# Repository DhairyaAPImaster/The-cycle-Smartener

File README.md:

# The Cycle Smartener
**(Makes the cycle kindda smart)**
### By Dhairya

## About "The Cycle Smartener"

So the Cycle smartener or TCS for short is basically this device that i designed that can be fitted on top of (almost) any modern cycle. Btw i made this cause i absolutelly love cycling and yeah having such a device would make the whole ride way more fun and interesting.

I plan on integrating TinyML (later) to also integrate AI into it so that it can do stuff like change the song or answer questions from voice commands. Alsoin next versions i plan on adding bluetooth so that one can connect their device - smart phone or something to it. and an sd card slot for one to put a micro sd in it to add music.

Btw it also has a 2.4inch LCD Display  (to displays whatever needs to be displayed).

## Folder Structure

`firmware/` - ESP32 firmware source code (C++)

`src/` - source files for PCB and CAD

`src/FreeCAD/` - mechanical CAD sources (open the .FCStd in FreeCAD)

`src/KiCAD/` - KiCad project files for the PCB

`Production/` - exports and fab outputs (gerbers, BOM, STLs)

`Production/PCB/` - gerbers, BOM, CPL files

`Production/CAD/` - exported STLs for the case

`images/` - screenshots and photos used in this README

## BOM with non PCB parts as well as PCB parts (with links)

Here's the parts list i kept while designing - both PCB parts and non-PCB components. i used the file `Production/BOM with non PCB parts too.csv` as the source.

| Item | Purpose | Qty | Unit Price (USD) | Total (USD) | Link |
| --- | --- | ---: | ---: | ---: | --- |
| Micro SD 16GB | For storage | 1 | $13.07 | $13.07 | [link](https://robu.in/product/sandisk-ultra-micro-sd-16gb-uhs-i-98mbs-r-class-10-memory-card/) |
| 40 Pin 2.54mm Male and Female Pin Headers | For connecting modules | 1 | $1.25 | $1.25 | [link](https://www.amazon.in/Super-Debug-Headers-Arduino-Prototype/dp/B09MZD3RBF) |
| Micro SD Card Reader Module | For storage/songs | 1 | $0.35 | $0.35 | [link](https://robu.in/product/micro-sd-card-module/) |
| 3mm Red LED | Status/Error Indicator | 11 | $0.01 | $0.10 | [link](https://robu.in/product/3mm-red-dip-led-pack-of-50/) |
| 3mm Green LED | Status/OK Indicator | 7 | $0.02 | $0.11 | [link](https://robu.in/product/5mm-green-surface-mount-led-pack-of-50/) |
| Tactile Push Button Switch 6x6 | Buttons | 1 Pack | $0.16 | $0.16 | [link](https://robu.in/product/6x6x5-tactile-push-button-switch/) |
| 10uF 25V Electrolytic Capacitor (Pack of 12) | Decoupling | 1 Pack | $0.83 | $0.83 | [link](https://www.amazon.in/10uF-25V-Electrolytic-Capacitor-Pack/dp/B08X2NSPZN) |
| 0.1µF Ceramic Capacitor (100nF) | Decoupling | 10 | $0.01 | $0.13 | [link](https://robu.in/product/100nf-50v-disc-capacitor/) |
| 150Ω Through-Hole Resistor | LED Current Limiting | 5 | $0.04 | $0.19 | [link](https://robu.in/product/mf25-150r-multicomp-pro-through-hole-resistor-150-ohm-mf25-series-250-mw-%C2%B1-1-axial-leaded-250-v/) |
| 10kΩ Through-Hole Resistor | Pull-up/Pull-down | 5 | $0.03 | $0.13 | [link](https://robu.in/product/mfr-25frf52-10k-yageo-metal-film-resistors-10k%CF%89-250mw-%C2%B1100ppm-%E2%84%83-%C2%B11-plugind2-4xl6-3mm-through-hole-resistors-rohs/) |
| 18650 Single Cell Holder | Battery Holder | 1 | $0.29 | $0.29 | [link](https://robu.in/product/1-x-18650-cell-box/) |
| 3.7V 2500mAh Li-Ion Battery | Power | 1 | $1.58 | $1.58 | [link](https://robocraze.com/products/3-7v-2500mah-18650-li-ion-battery?variant=43194107920608&country=IN&currency=INR&utm_medium=product_sync&utm_source=google&utm_content=sag_organic&utm_campaign=sag_organic&srsltid=AfmBOoojrg3iIbeikOa49Kg1J_byq0ZA_cZZ5BnBvvXHzwX-LQ-mY7_X_Ts&gclid=CjwKCAjw6rfSBhAqEiwA_yocphlz4TVfzvYZmMYIPGl8_hWx_POv68B57GqonKcBJzbM5ypkRMQ7fhoCPvMQAvD_BwE) |
| AMS1117-3.3V Voltage Regulator | Voltage Regulation | 2 | $0.09 | $0.19 | [link](https://robu.in/product/ams1117-3-3v-1a-sot-223-voltage-regulator-ic-pack-of-5-ics/) |
| TP4056 Type-C Charging Module | Li-Ion Charger | 1 | $0.17 | $0.17 | [link](https://robu.in/product/tp4056-1a-li-ion-battery-charging-board-micro-usb-with-current-protection-type-c-connector/) |
| INMP441 MEMS I2S Microphone Module | Audio Input | 1 | $4.58 | $4.58 | [link](https://www.flyrobo.in/inmp441-mems-high-precision-omnidirectional-microphone-module-i2s-interface-supports-esp32) |
| MAX98357 I2S 3W Class-D Audio Amplifier | Audio Output | 1 | $3.38 | $3.38 | [link](https://www.flyrobo.in/max98357-i2s-3w-class-d-audio-amplifier-module) |
| CP2102 USB to TTL UART Converter | Programming | 1 | $1.18 | $1.18 | [link](https://robu.in/product/cp-2102-6-pin/) |
| Waveshare 2.4" 240×320 LCD Display | User Interface | 1 | $11.09 | $11.09 | [link](https://robu.in/product/waveshare-240x320-general-2-4inch-lcd-display-module-65k-rgb/) |
| ESP32-WROOM-32U Wi-Fi + BLE Module | Main Microcontroller | 1 | $2.81 | $2.81 | [link](https://evelta.com/esp32-wroom-32u-wi-fi-ble-module-4mb-ipex-antenna-connector/?sku=136-ESP32-WROOM-32U-N4) |
| JLCPCB PCB Fabrication + Shipping | Custom PCB Manufacturing | 1 | $18.48 | $18.48 | [link](https://jlcpcb.com/) |
| JLCPCB Tax | Taxes | 1 | $7.40 | $7.40 | [link](https://jlcpcb.com/) |

| **Summary** | | | | |
| --- | --- | ---: | ---: | ---: |
| Electronics Components Total | | | | **$41.61** |
| JLCPCB (PCB + Shipping) | | | | **$18.48** |
| Tax | | | | **$7.40** |
| **Grand Total (USD)** | | | | **$67.49** |

***

## BOM with only PCB parts and no links (got from KiCAD)

<details>
<summary><b>Click to expand Bill of Materials</b></summary>

| Designator | Designation | Quantity | Footprint |
|---|---|---|---|
| C1, C2 | 10µF | 2 | CP_Radial_D5.0mm_P2.50mm |
| C3, C7, C8, C9 | 0.1uF | 4 | C_Disc_D5.0mm_W2.5mm_P5.00mm |
| C4 | 10uF | 1 | C_Disc_D5.0mm_W2.5mm_P5.00mm |
| D1 | GREEN LED | 1 | LED_D5.0mm |
| D2 | RED LED | 1 | LED_D5.0mm |
| J1 | TP4056 Module | 1 | PinHeader_1x02_P2.54mm_Vertical |
| J2 | AudioJack3 | 1 | Jack_3.5mm_CUI_SJ-3523-SMT_Horizontal |
| J3 | SD CARD READER | 1 | PinHeader_1x06_P2.54mm_Horizontal |
| J4 | J5A - INMP441 Left | 1 | PinHeader_1x03_P2.54mm_Vertical |
| J5 | J5B - INMP441 Right | 1 | PinHeader_1x06_P2.54mm_Vertical |
| J6 | UART_HEADER | 1 | PinHeader_1x08_P2.54mm_Vertical |
| J7 | Display connector | 1 | PinHeader_1x08_P2.54mm_Vertical |
| J8 | MAX 98357A_left | 1 | PinHeader_1x02_P2.54mm_Vertical |
| J9 | MAX 98357A_right | 1 | PinHeader_1x07_P2.54mm_Vertical |
| R1 | R | 1 | R_Axial_DIN0207_L6.3mm_D2.5mm_P10.16mm_Horizontal |
| R2 | 10k | 1 | R_Axial_DIN0207_L6.3mm_D2.5mm_P10.16mm_Horizontal |
| R4, R5 | 150 | 2 | R_Axial_DIN0207_L6.3mm_D2.5mm_P10.16mm_Horizontal |
| SW1, SW2 | SW_Push | 2 | SW_PUSH_6mm |
| U1 | ESP32-WROOM-32 | 1 | ESP32-WROOM-32 |
| U2 | AMS1117-3.3 | 1 | SOT-223-3_TabPin2 |

</details>

## How to Replicate

- Step 1 - Basically Just Clone or downlaod this repo from github. U can do this by either going to the code button on this repo page and pressing download Zip or u can clone this Repo Or you can go to the Releases on this repo and download the Zip File there too (the fastest way to download is like just going to code and pressing download Zip Or by cloning the Repo.)

- Step 2 - In the the production folder you will find the CAD and PCB folders.

- Step 3 - The CAD folder contains all the 3d Pritnable files for the case of the keyboard. If you wish to u can make any changes to the design or make your own design and use that instead.

- Step 4 - The PCB folder contains the Gerbers, BOM , and CPL files. These are the files that allow you to get the PCB manufactured from JLCPCB (im using JLCPCB) or any other PCB manufacturer(like PCBway or others).

- Step 5 - Upload the gerbers zip file in JLCPCB "Place order / get instant quote" Page (u will need to sign up to order but can get a quote without signing up)

- Step 6 - Change the colour of the PCB in the options JLC gives (if u use JLC PCB most of the times canging colours does not add any charge acc to what i know)

- Step 7 - Select PCBA if u want JLCPCB to assemble the PCB for you but ngl soldering all components by hand is cheaper and saves u a ton of money and also is pretty fun (im hand soldering all components)

- Step 8 - Upload the CPL and BOM files whe JLCPCB asks u to.

- Step 9 - Recheck the position of all components (i faced no problem with this as all components were in the correct place but i have faced issues with the placement in one of my other projects i made in KiCAD)
- Step 10 - Order the PCB

- Step 11 - if u dont have a 3d printer u can order the 3d model from JLC's JLC3DP but yeah all you have to do now is print the case and assemble the PCB in the case. (note u might have to trim down the spacers just a little)

- Step 12 - Get 8 M2 bolts and 8 heat insterts for it.

- Step 13 - Attatch the heat insrets into the case through the holes made for the hook. each hook has 4 holes for botlts.

- Step 14 - Position the hook from below on the cycles bar and position the case itself above it and then carefully screw in the screws securing the device to your cycle!!!!!!

- DONE!!!!! 

## Images

## License and Credits

**License -->**
This project is licensed under the MIT License — see the [LICENSE](LICENSE) file for details.

**Credits -->**
***I used the following for making this project***

- ***KiCAD*** - For PCB design
- ***FreeCAD*** - For designing the Case
- **[APX HUB by @Gabouin](https://github.com/Gabouin/APX-USB-HUB)** - Readme template

## Final Notes

**Firmware Note --->  Used a friend help and also used AI (github copilot) too to like help me write a part of it as well ngl I suck at C++ also like used github copilot to like arrange the code in a more readable manner.**

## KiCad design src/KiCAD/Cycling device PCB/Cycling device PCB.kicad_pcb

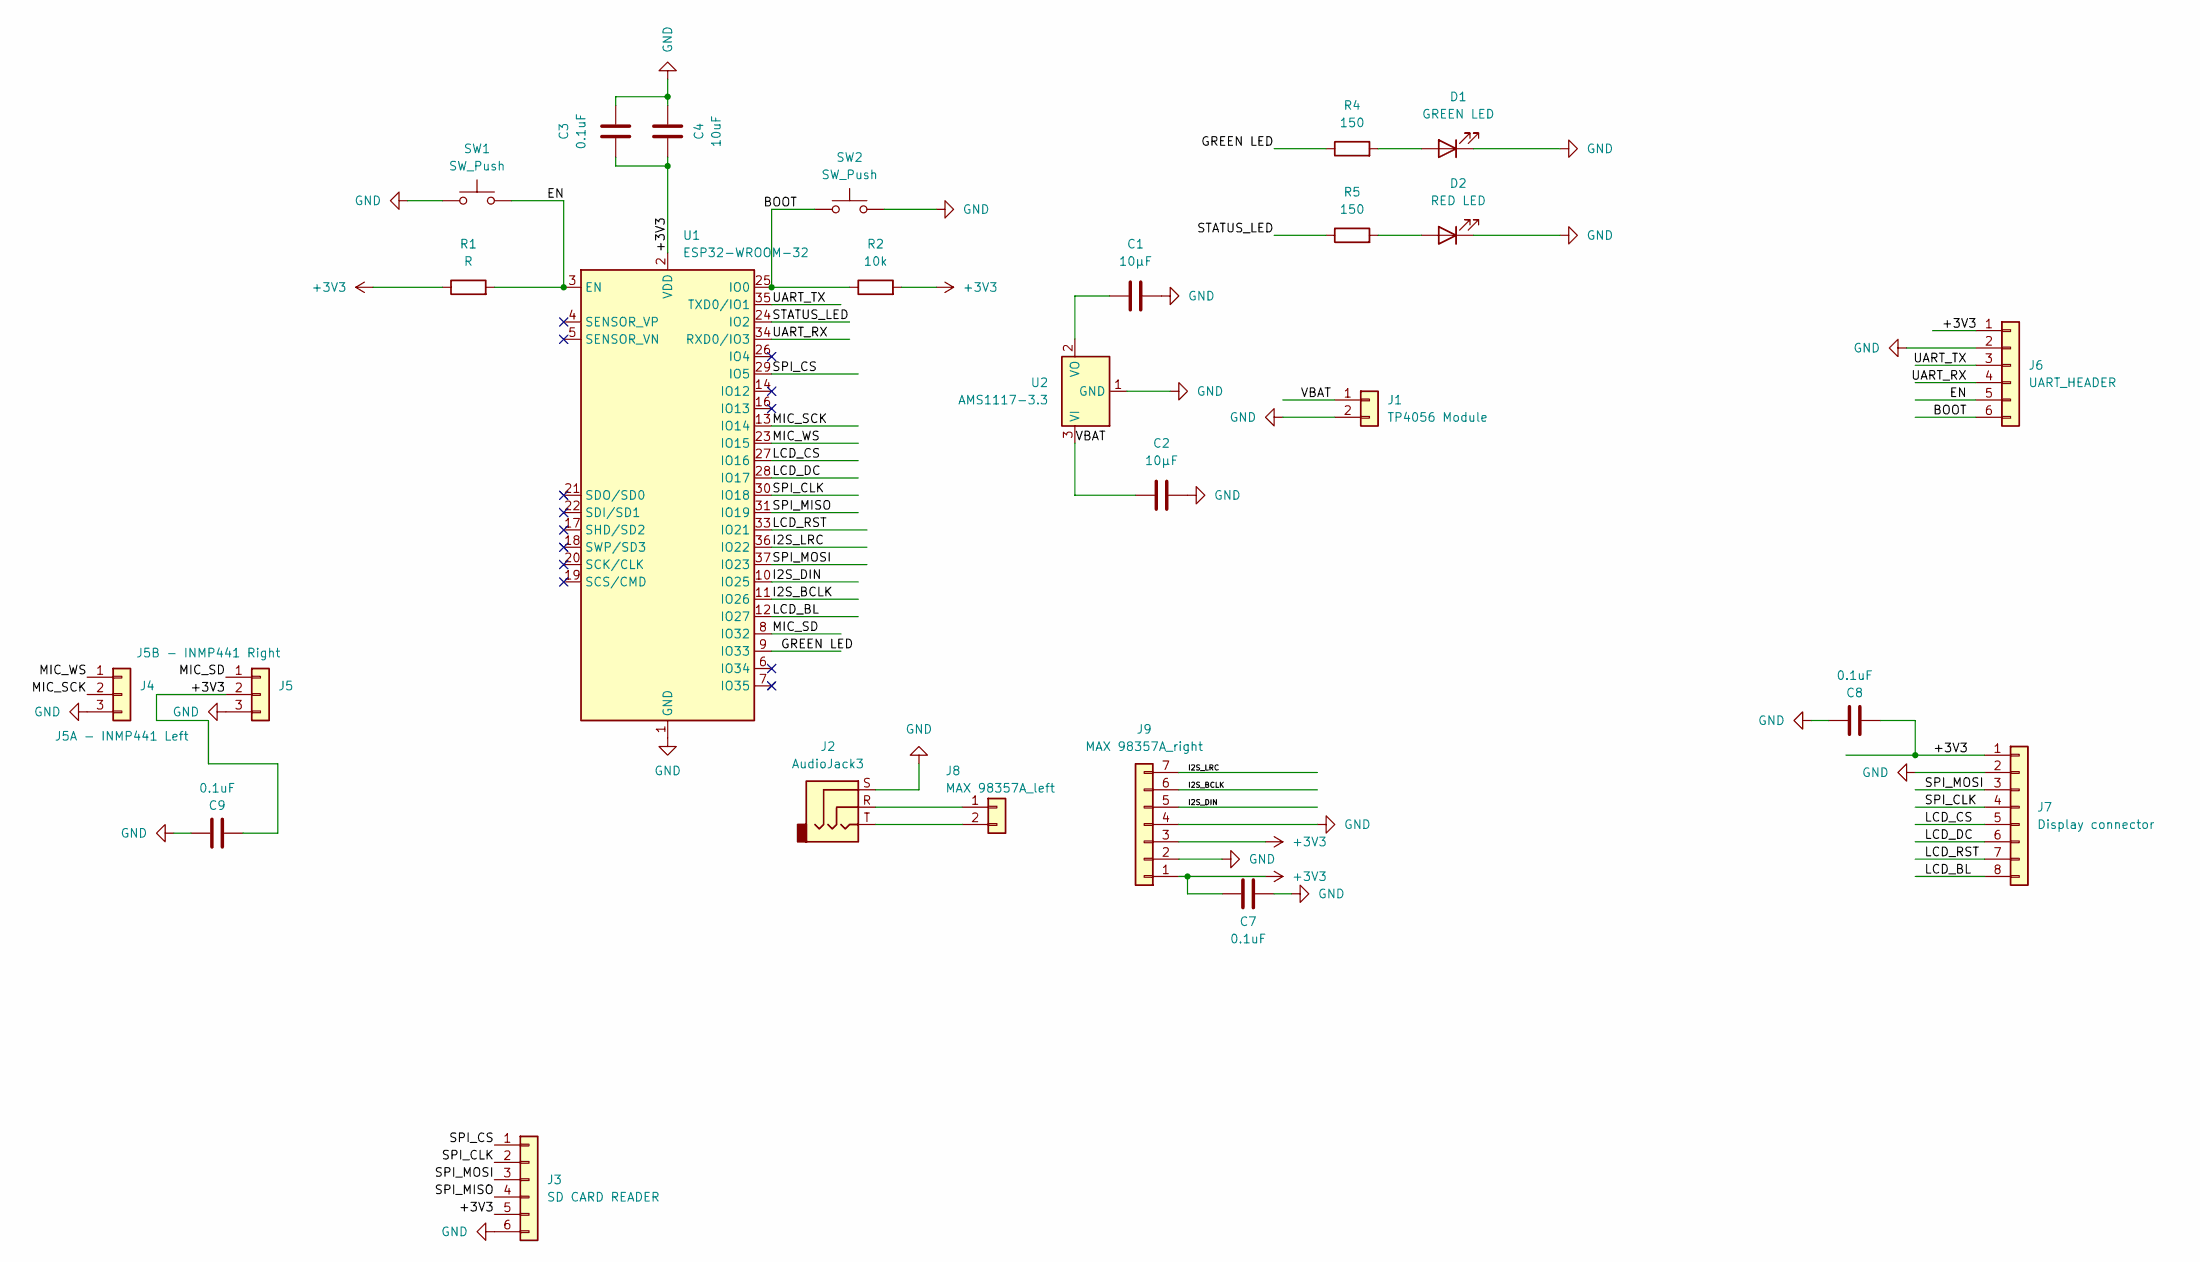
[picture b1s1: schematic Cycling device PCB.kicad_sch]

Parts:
C1, C2: 10µF; CP_Radial_D5.0mm_P2.50mm
C3, C7, C8, C9: 0.1uF; C_Disc_D5.0mm_W2.5mm_P5.00mm
C4: 10uF; C_Disc_D5.0mm_W2.5mm_P5.00mm
D1: GREEN LED; LED_D5.0mm
D2: RED LED; LED_D5.0mm
J1: TP4056 Module; PinHeader_1x02_P2.54mm_Vertical
J2: AudioJack3; Jack_3.5mm_CUI_SJ-3523-SMT_Horizontal
J3: SD CARD READER; PinHeader_1x06_P2.54mm_Horizontal
J4: J5A - INMP441 Left; PinHeader_1x03_P2.54mm_Vertical
J5: J5B - INMP441 Right; PinHeader_1x06_P2.54mm_Vertical
J6: UART_HEADER; PinHeader_1x08_P2.54mm_Vertical
J7: Display connector; PinHeader_1x08_P2.54mm_Vertical
J8: MAX 98357A_left; PinHeader_1x02_P2.54mm_Vertical
J9: MAX 98357A_right; PinHeader_1x07_P2.54mm_Vertical
R1: R; R_Axial_DIN0207_L6.3mm_D2.5mm_P10.16mm_Horizontal
R2: 10k; R_Axial_DIN0207_L6.3mm_D2.5mm_P10.16mm_Horizontal
R4, R5: 150; R_Axial_DIN0207_L6.3mm_D2.5mm_P10.16mm_Horizontal
SW1, SW2: SW_Push; SW_PUSH_6mm
U1: ESP32-WROOM-32
U2: AMS1117-3.3; SOT-223-3_TabPin2

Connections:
+3V3: C3.1, C4.1, C7.2, C8.2, C9.2, J3.5, J5.2, J6.1, J7.1, J9.1, J9.3, R1.1, R2.2, U1.2 (VDD)
/BOOT: J6.6, R2.1, SW2.1, U1.25 (IO0)
/EN: J6.5, R1.2, SW1.2, U1.3 (EN)
/GREEN LED: R4.1, U1.9 (IO33)
/I2S_BCLK: J9.6, U1.11 (IO26)
/I2S_DIN: J9.5, U1.10 (IO25)
/I2S_LRC: J9.7, U1.36 (IO22)
/LCD_BL: J7.8, U1.12 (IO27)
/LCD_CS: J7.5, U1.27 (IO16)
/LCD_DC: J7.6, U1.28 (IO17)
/LCD_RST: J7.7, U1.33 (IO21)
/MIC_SCK: J4.2, U1.13 (IO14)
/MIC_SD: J5.1, U1.8 (IO32)
/MIC_WS: J4.1, U1.23 (IO15)
/SPI_CLK: J3.2, J7.4, U1.30 (IO18)
/SPI_CS: J3.1, U1.29 (IO5)
/SPI_MISO: J3.4, U1.31 (IO19)
/SPI_MOSI: J3.3, J7.3, U1.37 (IO23)
/STATUS_LED: R5.1, U1.24 (IO2)
/UART_RX: J6.4, U1.34 (RXD0/IO3)
/UART_TX: J6.3, U1.35 (TXD0/IO1)
/VBAT: C2.1, J1.1, U2.3 (VI)
GND: C1.2, C2.2, C3.2, C4.2, C7.1, C8.1, C9.1, D1.1 (K), D2.1 (K), J1.2, J2.S, J3.6, J4.3, J5.3, J6.2, J7.2, J9.2, J9.4, SW1.1, SW2.2, U1.1 (GND), U1.15 (GND), U1.38 (GND), U1.39 (GND), U2.1 (GND)
unnamed: D1.2 (A), R4.2
unnamed: D2.2 (A), R5.2
unnamed: J2.R, J8.1
unnamed: J2.T, J8.2
unnamed: C1.1, U2.2 (VO)

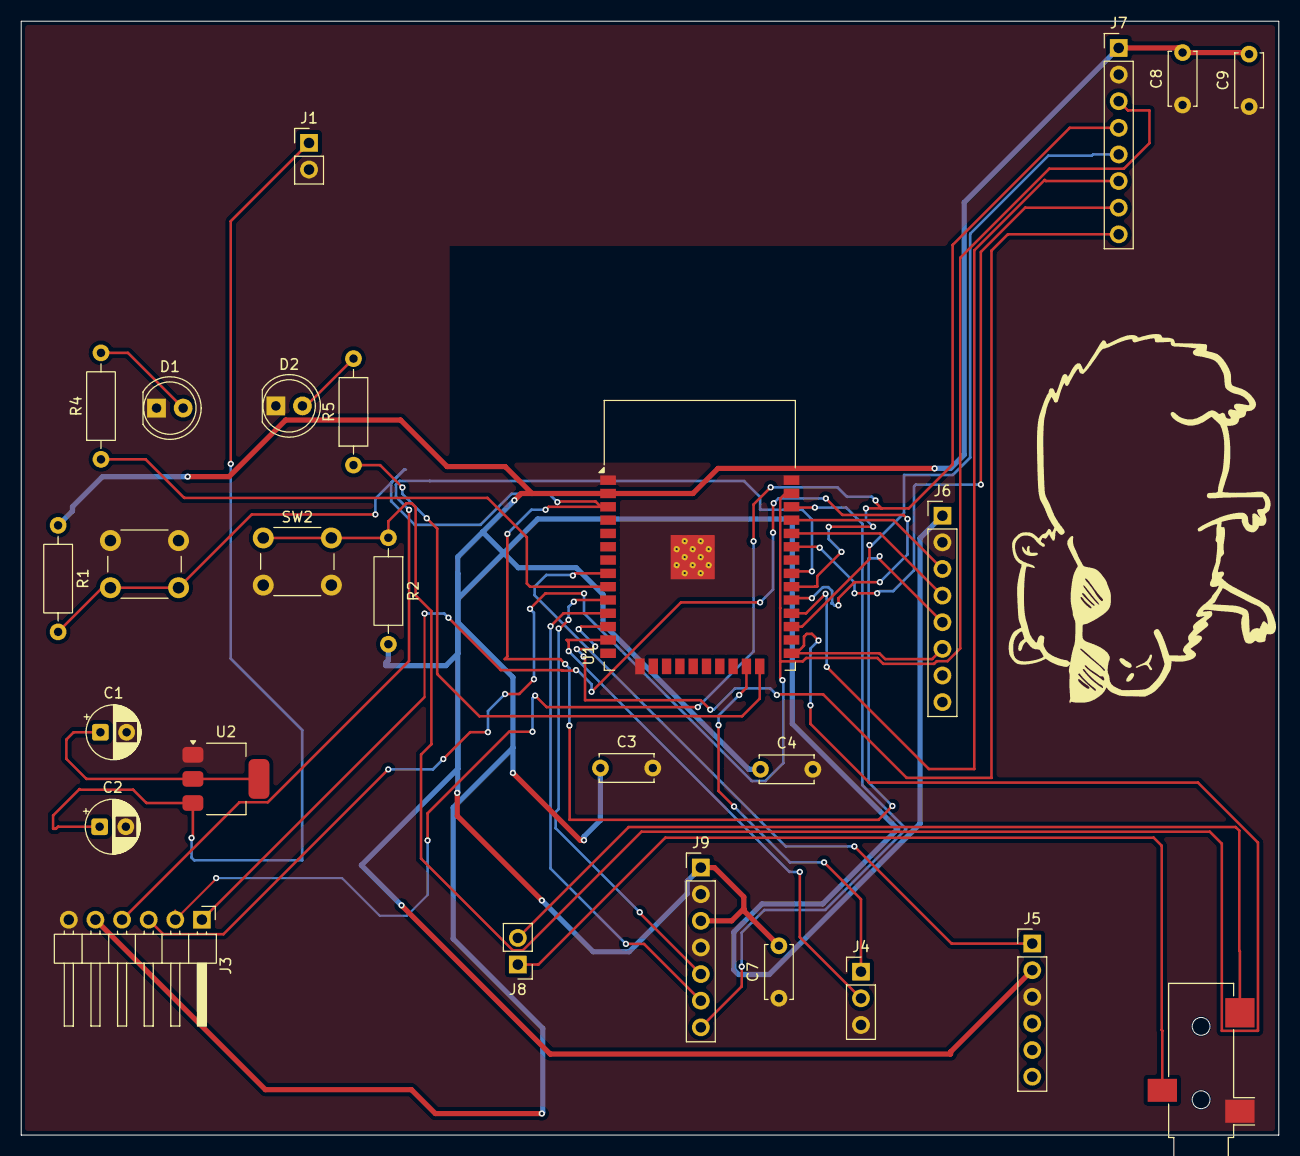
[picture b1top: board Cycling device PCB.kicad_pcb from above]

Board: 2 copper layers, 120.0 x 106.3 mm, 26 parts (0 on the bottom side), 28 nets.

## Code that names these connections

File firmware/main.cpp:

#include <Arduino.h>
#include <SPI.h>
#include <SD.h>
#include <driver/i2s.h>
#include <Preferences.h>
#include <Wire.h>

#if __has_include(<Adafruit_GFX.h>)
#include <Adafruit_GFX.h>
#include <Adafruit_ILI9341.h>
#define HAS_LCD_LIB 1
#else
#define HAS_LCD_LIB 0
#endif

namespace {
constexpr gpio_num_t PIN_SD_CS = GPIO_NUM_5;
constexpr gpio_num_t PIN_LCD_CS = GPIO_NUM_16;
constexpr gpio_num_t PIN_LCD_DC = GPIO_NUM_17;
constexpr gpio_num_t PIN_LCD_RST = GPIO_NUM_21;
constexpr gpio_num_t PIN_LCD_BL = GPIO_NUM_27;
constexpr gpio_num_t PIN_SPI_SCK = GPIO_NUM_18;
constexpr gpio_num_t PIN_SPI_MOSI = GPIO_NUM_23;
constexpr gpio_num_t PIN_SPI_MISO = GPIO_NUM_19;

constexpr gpio_num_t PIN_I2S_BCLK = GPIO_NUM_26;
constexpr gpio_num_t PIN_I2S_LRCLK = GPIO_NUM_22;
constexpr gpio_num_t PIN_I2S_DIN = GPIO_NUM_25;
constexpr gpio_num_t PIN_I2S_MIC_BCLK = GPIO_NUM_14;
constexpr gpio_num_t PIN_I2S_MIC_WS = GPIO_NUM_15;
constexpr gpio_num_t PIN_I2S_MIC_SD = GPIO_NUM_32;
constexpr gpio_num_t PIN_I2S_AMP_SD = GPIO_NUM_25;

constexpr gpio_num_t PIN_STATUS_LED = GPIO_NUM_2;
constexpr gpio_num_t PIN_BOOT_BUTTON = GPIO_NUM_0;
constexpr gpio_num_t PIN_BUTTON_1 = GPIO_NUM_34;
constexpr gpio_num_t PIN_BUTTON_2 = GPIO_NUM_35;

constexpr uint32_t AUDIO_SAMPLE_RATE = 16000;
constexpr size_t AUDIO_FRAME_COUNT = 256;

Preferences preferences;

#if HAS_LCD_LIB
Adafruit_ILI9341 lcd(PIN_LCD_CS, PIN_LCD_DC, PIN_LCD_RST);
#endif

bool sdReady = false;
bool lcdReady = false;

void setBacklight(bool enabled) {
  digitalWrite(static_cast<int>(PIN_LCD_BL), enabled ? HIGH : LOW);
}

void setStatusLed(bool enabled) {
  digitalWrite(static_cast<int>(PIN_STATUS_LED), enabled ? HIGH : LOW);
}

void drawBootScreen(const char *line1, const char *line2, uint16_t color) {
#if HAS_LCD_LIB
  if (!lcdReady) {
    return;
  }
  lcd.fillScreen(ST77XX_BLACK);
  lcd.setTextWrap(true);
  lcd.setTextSize(2);
  lcd.setTextColor(color);
  lcd.setCursor(12, 24);
  lcd.println(line1);
  lcd.setCursor(12, 64);
  lcd.setTextSize(1);
  lcd.println(line2);
#else
  (void)line1;
  (void)line2;
  (void)color;
#endif
}

void initDisplay() {
  pinMode(static_cast<int>(PIN_LCD_BL), OUTPUT);
  setBacklight(true);

#if HAS_LCD_LIB
  pinMode(static_cast<int>(PIN_LCD_CS), OUTPUT);
  pinMode(static_cast<int>(PIN_LCD_DC), OUTPUT);
  pinMode(static_cast<int>(PIN_LCD_RST), OUTPUT);
  SPI.begin(static_cast<uint8_t>(PIN_SPI_SCK), static_cast<uint8_t>(PIN_SPI_MISO), static_cast<uint8_t>(PIN_SPI_MOSI), static_cast<uint8_t>(PIN_LCD_CS));
  lcd.begin();
  lcd.setRotation(1);
  lcdReady = true;
  drawBootScreen("Cycle Smartener", "LCD ready", ST77XX_GREEN);
#else
  lcdReady = false;
#endif
}

void initSdCard() {
  SPI.begin(static_cast<uint8_t>(PIN_SPI_SCK), static_cast<uint8_t>(PIN_SPI_MISO), static_cast<uint8_t>(PIN_SPI_MOSI), static_cast<uint8_t>(PIN_SD_CS));
  pinMode(static_cast<int>(PIN_SD_CS), OUTPUT);
  digitalWrite(static_cast<int>(PIN_SD_CS), HIGH);

  sdReady = SD.begin(static_cast<uint8_t>(PIN_SD_CS), SPI, 20000000);
  if (sdReady) {
    Serial.println("SD card mounted");
  } else {
    Serial.println("SD card mount failed");
  }
}

bool initAudioOutput() {
  const i2s_config_t config = {
      .mode = static_cast<i2s_mode_t>(I2S_MODE_MASTER | I2S_MODE_TX),
      .sample_rate = static_cast<int>(AUDIO_SAMPLE_RATE),
      .bits_per_sample = I2S_BITS_PER_SAMPLE_16BIT,
      .channel_format = I2S_CHANNEL_FMT_RIGHT_LEFT,
      .communication_format = I2S_COMM_FORMAT_STAND_I2S,
      .intr_alloc_flags = ESP_INTR_FLAG_LEVEL1,
      .dma_buf_count = 8,
      .dma_buf_len = 256,
      .use_apll = false,
      .tx_desc_auto_clear = true,
      .fixed_mclk = 0,
  };

  const i2s_pin_config_t pins = {
      .bck_io_num = static_cast<int>(PIN_I2S_BCLK),
      .ws_io_num = static_cast<int>(PIN_I2S_LRCLK),
      .data_out_num = static_cast<int>(PIN_I2S_DIN),
      .data_in_num = I2S_PIN_NO_CHANGE,
  };

  if (i2s_driver_install(I2S_NUM_0, &config, 0, nullptr) != ESP_OK) {
    return false;
  }
  if (i2s_set_pin(I2S_NUM_0, &pins) != ESP_OK) {
    return false;
  }
  return true;
}

bool initMicInput() {
  const i2s_config_t config = {
      .mode = static_cast<i2s_mode_t>(I2S_MODE_MASTER | I2S_MODE_RX),
      .sample_rate = static_cast<int>(AUDIO_SAMPLE_RATE),
      .bits_per_sample = I2S_BITS_PER_SAMPLE_32BIT,
      .channel_format = I2S_CHANNEL_FMT_ONLY_LEFT,
      .communication_format = I2S_COMM_FORMAT_STAND_I2S,
      .intr_alloc_flags = ESP_INTR_FLAG_LEVEL1,
      .dma_buf_count = 8,
      .dma_buf_len = 256,
      .use_apll = false,
      .tx_desc_auto_clear = false,
      .fixed_mclk = 0,
  };

  const i2s_pin_config_t pins = {
      .bck_io_num = static_cast<int>(PIN_I2S_MIC_BCLK),
      .ws_io_num = static_cast<int>(PIN_I2S_MIC_WS),
      .data_out_num = I2S_PIN_NO_CHANGE,
      .data_in_num = static_cast<int>(PIN_I2S_MIC_SD),
  };

  if (i2s_driver_install(I2S_NUM_1, &config, 0, nullptr) != ESP_OK) {
    return false;
  }
  if (i2s_set_pin(I2S_NUM_1, &pins) != ESP_OK) {
    return false;
  }
  return true;
}

void showStorageSummary() {
#if HAS_LCD_LIB
  if (!lcdReady) {
    return;
  }
  lcd.fillScreen(ST77XX_BLACK);
  lcd.setCursor(0, 0);
  lcd.setTextSize(2);
  lcd.setTextColor(ST77XX_CYAN);
  lcd.println("Cycle Smartener");
  lcd.setTextSize(1);
  lcd.setTextColor(ST77XX_WHITE);
  lcd.print("SD: ");
  lcd.println(sdReady ? "ready" : "missing");
  lcd.print("Audio: ");
  lcd.println("I2S active");
  lcd.print("Buttons: ");
  lcd.println("boot / user");
#endif
}

void readButtons() {
  const bool bootPressed = digitalRead(static_cast<int>(PIN_BOOT_BUTTON)) == LOW;
  const bool button1Pressed = digitalRead(static_cast<int>(PIN_BUTTON_1)) == LOW;
  const bool button2Pressed = digitalRead(static_cast<int>(PIN_BUTTON_2)) == LOW;

  if (bootPressed) {
    setStatusLed(true);
  } else {
    setStatusLed(false);
  }

  if (button1Pressed) {
    preferences.putUInt("lastButton", 1);
  }
  if (button2Pressed) {
    preferences.putUInt("lastButton", 2);
  }
}

void readMicLevel() {
  static int32_t samples[AUDIO_FRAME_COUNT];
  size_t bytesRead = 0;
  esp_err_t result = i2s_read(I2S_NUM_1, samples, sizeof(samples), &bytesRead, 0);
  if (result != ESP_OK || bytesRead == 0) {
    return;
  }

  const size_t sampleCount = bytesRead / sizeof(int32_t);
  int64_t sum = 0;
  for (size_t index = 0; index < sampleCount; ++index) {
    sum += abs(samples[index] >> 14);
  }
  const uint32_t level = sampleCount ? static_cast<uint32_t>(sum / static_cast<int64_t>(sampleCount)) : 0;
  preferences.putUInt("micLevel", level);
}

void logSystemState() {
  Serial.printf("SD=%s LCD=%s Mic=%s\n", sdReady ? "ready" : "missing", lcdReady ? "ready" : "missing", "ready");
}
}  // namespace

void setup() {
  Serial.begin(115200);
  delay(200);

  pinMode(static_cast<int>(PIN_STATUS_LED), OUTPUT);
  pinMode(static_cast<int>(PIN_BOOT_BUTTON), INPUT_PULLUP);
  pinMode(static_cast<int>(PIN_BUTTON_1), INPUT);
  pinMode(static_cast<int>(PIN_BUTTON_2), INPUT);

  preferences.begin("cycle", false);

  initDisplay();
  initSdCard();

  const bool micReady = initMicInput();
  const bool ampReady = initAudioOutput();

  Serial.printf("Mic init: %s\n", micReady ? "ok" : "failed");
  Serial.printf("Amp init: %s\n", ampReady ? "ok" : "failed");

  showStorageSummary();
  logSystemState();
}

void loop() {
  static uint32_t lastUiRefresh = 0;
  static uint32_t lastMicRead = 0;

  readButtons();

  const uint32_t now = millis();
  if (now - lastMicRead >= 40) {
    lastMicRead = now;
    readMicLevel();
  }

  if (now - lastUiRefresh >= 1000) {
    lastUiRefresh = now;
    showStorageSummary();
    logSystemState();
  }

  delay(5);
}

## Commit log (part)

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2026-06-17 Add initial README with project description
    Added the title and banner
2026-06-18 added the CAD production files
2026-06-18 renamed a folder
2026-06-18 designed the handle clamps to attatch to cycle and also updated the CAD files
2026-06-18 added readme
2026-06-19 Revise README for Cycle Smartener project details
    Updated README to provide detailed information about the Cycle Smartener project, including features, repo structure, usage instructions, and licensing.
2026-06-19 Update README with project details and features
    Added project description and features for The Cycle Smartener.
2026-06-19 Almost finished the full readme
    Added folder structure, BOM, replication steps, images, and credits sections to README.
2026-06-19 updated formating in readme
2026-06-19 folder structure formatting
    Added detailed folder structure information to README.
2026-06-19 added collapsable and tabular BOM in the Readme.
2026-06-19 aded a new BOM with all links and also all the non PCB components
2026-06-26 added the .stl files in a folder specifically made for the stl files. also added the C++ firmware code
